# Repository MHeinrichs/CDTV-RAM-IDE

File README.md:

[This project moved to gitlab on the day M$ bought github](https://gitlab.com/MHeinrichs/CDTV-RAM-IDE)

The new repository is at: https://gitlab.com/MHeinrichs/CDTV-RAM-IDE

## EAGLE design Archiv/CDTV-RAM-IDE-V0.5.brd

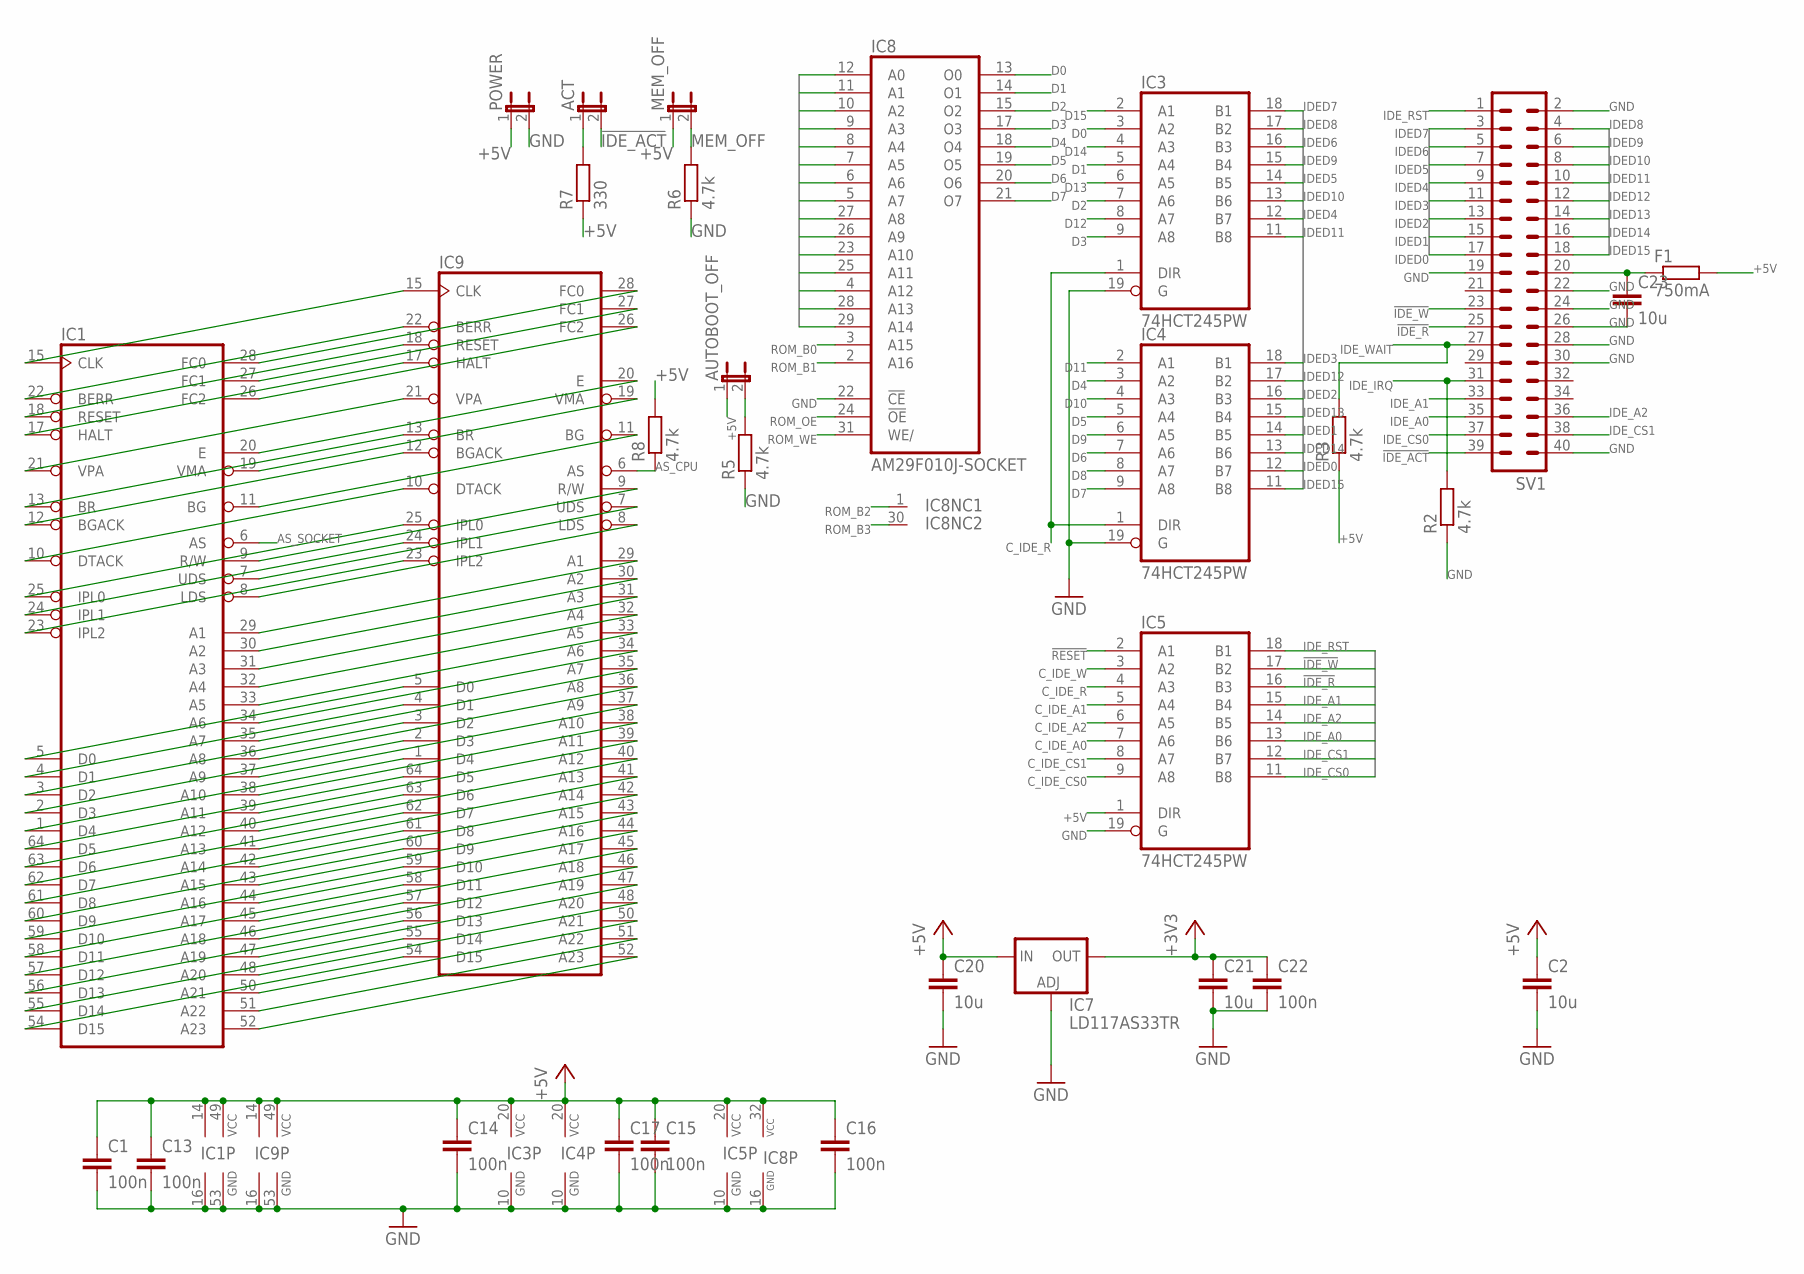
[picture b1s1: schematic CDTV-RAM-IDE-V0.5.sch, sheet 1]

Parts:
ACT: JP1E; JP1
AUTOBOOT_OFF: JP1E; JP1
C1, C13, C14, C15, C16, C17, C22: 100n; C0603K
C2, C20, C21, C23: 10u; C0805K
F1: 750mA; R2512
IC1, IC9: MC68000PROUND-PAD-BIG-HOLE; DIL64-ROUND-BIGHOLE
IC3, IC4, IC5: 74HCT245PW; TSSOP20
IC7: LD117AS33TR; SOT223
IC8: AM29F010J-SOCKET; PLCC-32-SMT-TT
MEM_OFF: JP1E; JP1
POWER: JP1E; JP1
R2, R3, R5, R6, R8: 4.7k; R0603
R7: 330; R0603
SV1: ML40

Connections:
!BERR: IC1.22 (BERR), IC9.22 (BERR); also elsewhere on the board
!BG: IC1.11 (BG), IC9.11 (BG)
!BGACK: IC1.12 (BGACK), IC9.12 (BGACK); also elsewhere on the board
!BR: IC1.13 (BR), IC9.13 (BR)
!DTACK: IC1.10 (DTACK), IC9.10 (DTACK); also elsewhere on the board
!HALT: IC1.17 (HALT), IC9.17 (HALT)
!IDE_ACT: ACT.2, SV1.39
!IDE_R: IC5.16 (B3), SV1.25
!IDE_W: IC5.17 (B2), SV1.23
!LDS: IC1.8 (LDS), IC9.8 (LDS); also elsewhere on the board
!RESET: IC1.18 (RESET), IC5.2 (A1), IC9.18 (RESET); also elsewhere on the board
!UDS: IC1.7 (UDS), IC9.7 (UDS); also elsewhere on the board
+3V3: C21.1, C22.1, IC7.2 (OUT), IC7.4 (OUT); also elsewhere on the board
+5V: AUTOBOOT_OFF.1, C1.1, C2.1, C13.1, C14.1, C15.1, C16.1, C17.1, C20.1, F1.2, IC1.14 (VCC), IC1.49 (VCC), IC3.20 (VCC), IC4.20 (VCC), IC5.1 (DIR), IC5.20 (VCC), IC7.3 (IN), IC8.32 (VCC), IC9.14 (VCC), IC9.49 (VCC), MEM_OFF.1, POWER.1, R3.1, R7.1, R8.2; also elsewhere on the board
A1: IC1.29 (A1), IC8.12 (A0), IC9.29 (A1); also elsewhere on the board
A2: IC1.30 (A2), IC8.11 (A1), IC9.30 (A2); also elsewhere on the board
A3: IC1.31 (A3), IC8.10 (A2), IC9.31 (A3); also elsewhere on the board
A4: IC1.32 (A4), IC8.9 (A3), IC9.32 (A4); also elsewhere on the board
A5: IC1.33 (A5), IC8.8 (A4), IC9.33 (A5); also elsewhere on the board
A6: IC1.34 (A6), IC8.7 (A5), IC9.34 (A6); also elsewhere on the board
A7: IC1.35 (A7), IC8.6 (A6), IC9.35 (A7); also elsewhere on the board
A8: IC1.36 (A8), IC8.5 (A7), IC9.36 (A8); also elsewhere on the board
A9: IC1.37 (A9), IC8.27 (A8), IC9.37 (A9); also elsewhere on the board
A10: IC1.38 (A10), IC8.26 (A9), IC9.38 (A10); also elsewhere on the board
A11: IC1.39 (A11), IC8.23 (A10), IC9.39 (A11); also elsewhere on the board
A12: IC1.40 (A12), IC8.25 (A11), IC9.40 (A12); also elsewhere on the board
A13: IC1.41 (A13), IC8.4 (A12), IC9.41 (A13); also elsewhere on the board
A14: IC1.42 (A14), IC8.28 (A13), IC9.42 (A14); also elsewhere on the board
A15: IC1.43 (A15), IC8.29 (A14), IC9.43 (A15); also elsewhere on the board
A16: IC1.44 (A16), IC9.44 (A16); also elsewhere on the board
A17: IC1.45 (A17), IC9.45 (A17); also elsewhere on the board
A18: IC1.46 (A18), IC9.46 (A18); also elsewhere on the board
A19: IC1.47 (A19), IC9.47 (A19); also elsewhere on the board
A20: IC1.48 (A20), IC9.48 (A20); also elsewhere on the board
A21: IC1.50 (A21), IC9.50 (A21); also elsewhere on the board
A22: IC1.51 (A22), IC9.51 (A22); also elsewhere on the board
A23: IC1.52 (A23), IC9.52 (A23); also elsewhere on the board
AS_CPU: IC9.6 (AS), R8.1; also elsewhere on the board
AS_SOCKET: IC1.6 (AS); also elsewhere on the board
AUTO_BOOT_OFF: AUTOBOOT_OFF.2, R5.2; also elsewhere on the board
CLK: IC1.15 (CLK), IC9.15 (CLK); also elsewhere on the board
C_IDE_A0: IC5.7 (A6); also elsewhere on the board
C_IDE_A1: IC5.5 (A4); also elsewhere on the board
C_IDE_A2: IC5.6 (A5); also elsewhere on the board
C_IDE_CS0: IC5.9 (A8); also elsewhere on the board
C_IDE_CS1: IC5.8 (A7); also elsewhere on the board
C_IDE_R: IC3.1 (DIR), IC4.1 (DIR), IC5.4 (A3); also elsewhere on the board
C_IDE_W: IC5.3 (A2); also elsewhere on the board
D0: IC1.5 (D0), IC3.3 (A2), IC8.13 (O0), IC9.5 (D0); also elsewhere on the board
D1: IC1.4 (D1), IC3.5 (A4), IC8.14 (O1), IC9.4 (D1); also elsewhere on the board
D2: IC1.3 (D2), IC3.7 (A6), IC8.15 (O2), IC9.3 (D2); also elsewhere on the board
D3: IC1.2 (D3), IC3.9 (A8), IC8.17 (O3), IC9.2 (D3); also elsewhere on the board
D4: IC1.1 (D4), IC4.3 (A2), IC8.18 (O4), IC9.1 (D4); also elsewhere on the board
D5: IC1.64 (D5), IC4.5 (A4), IC8.19 (O5), IC9.64 (D5); also elsewhere on the board
D6: IC1.63 (D6), IC4.7 (A6), IC8.20 (O6), IC9.63 (D6); also elsewhere on the board
D7: IC1.62 (D7), IC4.9 (A8), IC8.21 (O7), IC9.62 (D7); also elsewhere on the board
D8: IC1.61 (D8), IC4.8 (A7), IC9.61 (D8); also elsewhere on the board
D9: IC1.60 (D9), IC4.6 (A5), IC9.60 (D9); also elsewhere on the board
D10: IC1.59 (D10), IC4.4 (A3), IC9.59 (D10); also elsewhere on the board
D11: IC1.58 (D11), IC4.2 (A1), IC9.58 (D11); also elsewhere on the board
D12: IC1.57 (D12), IC3.8 (A7), IC9.57 (D12); also elsewhere on the board
D13: IC1.56 (D13), IC3.6 (A5), IC9.56 (D13); also elsewhere on the board
D14: IC1.55 (D14), IC3.4 (A3), IC9.55 (D14); also elsewhere on the board
D15: IC1.54 (D15), IC3.2 (A1), IC9.54 (D15); also elsewhere on the board
E: IC1.20 (E), IC9.20 (E)
FC0: IC1.28 (FC0), IC9.28 (FC0)
FC1: IC1.27 (FC1), IC9.27 (FC1)
FC2: IC1.26 (FC2), IC9.26 (FC2)
GND: C1.2, C2.2, C13.2, C14.2, C15.2, C16.2, C17.2, C20.2, C21.2, C22.2, C23.2, IC1.16 (GND), IC1.53 (GND), IC3.10 (GND), IC3.19 (G), IC4.10 (GND), IC4.19 (G), IC5.10 (GND), IC5.19 (G), IC7.1 (ADJ), IC8.16 (GND), IC8.22 (!CE), IC9.16 (GND), IC9.53 (GND), POWER.2, R2.1, R5.1, R6.1, SV1.2, SV1.19, SV1.22, SV1.24, SV1.26, SV1.28, SV1.30, SV1.40; also elsewhere on the board
IDED0: IC4.12 (B7), SV1.17
IDED1: IC4.14 (B5), SV1.15
IDED2: IC4.16 (B3), SV1.13
IDED3: IC4.18 (B1), SV1.11
IDED4: IC3.12 (B7), SV1.9
IDED5: IC3.14 (B5), SV1.7
IDED6: IC3.16 (B3), SV1.5
IDED7: IC3.18 (B1), SV1.3
IDED8: IC3.17 (B2), SV1.4
IDED9: IC3.15 (B4), SV1.6
IDED10: IC3.13 (B6), SV1.8
IDED11: IC3.11 (B8), SV1.10
IDED12: IC4.17 (B2), SV1.12
IDED13: IC4.15 (B4), SV1.14
IDED14: IC4.13 (B6), SV1.16
IDED15: IC4.11 (B8), SV1.18
IDE_A0: IC5.13 (B6), SV1.35
IDE_A1: IC5.15 (B4), SV1.33
IDE_A2: IC5.14 (B5), SV1.36
IDE_CS0: IC5.11 (B8), SV1.37
IDE_CS1: IC5.12 (B7), SV1.38
IDE_IRQ: R2.2, SV1.31; also elsewhere on the board
IDE_RST: IC5.18 (B1), SV1.1
IDE_WAIT: R3.2, SV1.27; also elsewhere on the board
IPL0: IC1.25 (IPL0), IC9.25 (IPL0)
IPL1: IC1.24 (IPL1), IC9.24 (IPL1)
IPL2: IC1.23 (IPL2), IC9.23 (IPL2)
KEY_PIN_POWER: C23.1, F1.1, SV1.20
MEM_OFF: MEM_OFF.2, R6.2; also elsewhere on the board
unnamed: ACT.1, R7.2
R/W: IC1.9 (R/W), IC9.9 (R/W); also elsewhere on the board
ROM_B0: IC8.3 (A15); also elsewhere on the board
ROM_B1: IC8.2 (A16); also elsewhere on the board
ROM_B2: IC8.1 (NC); also elsewhere on the board
ROM_B3: IC8.30 (NC); also elsewhere on the board
ROM_OE: IC8.24 (!OE); also elsewhere on the board
ROM_WE: IC8.31 (WE/); also elsewhere on the board
VMA: IC1.19 (VMA), IC9.19 (VMA)
VPA: IC1.21 (VPA), IC9.21 (VPA)

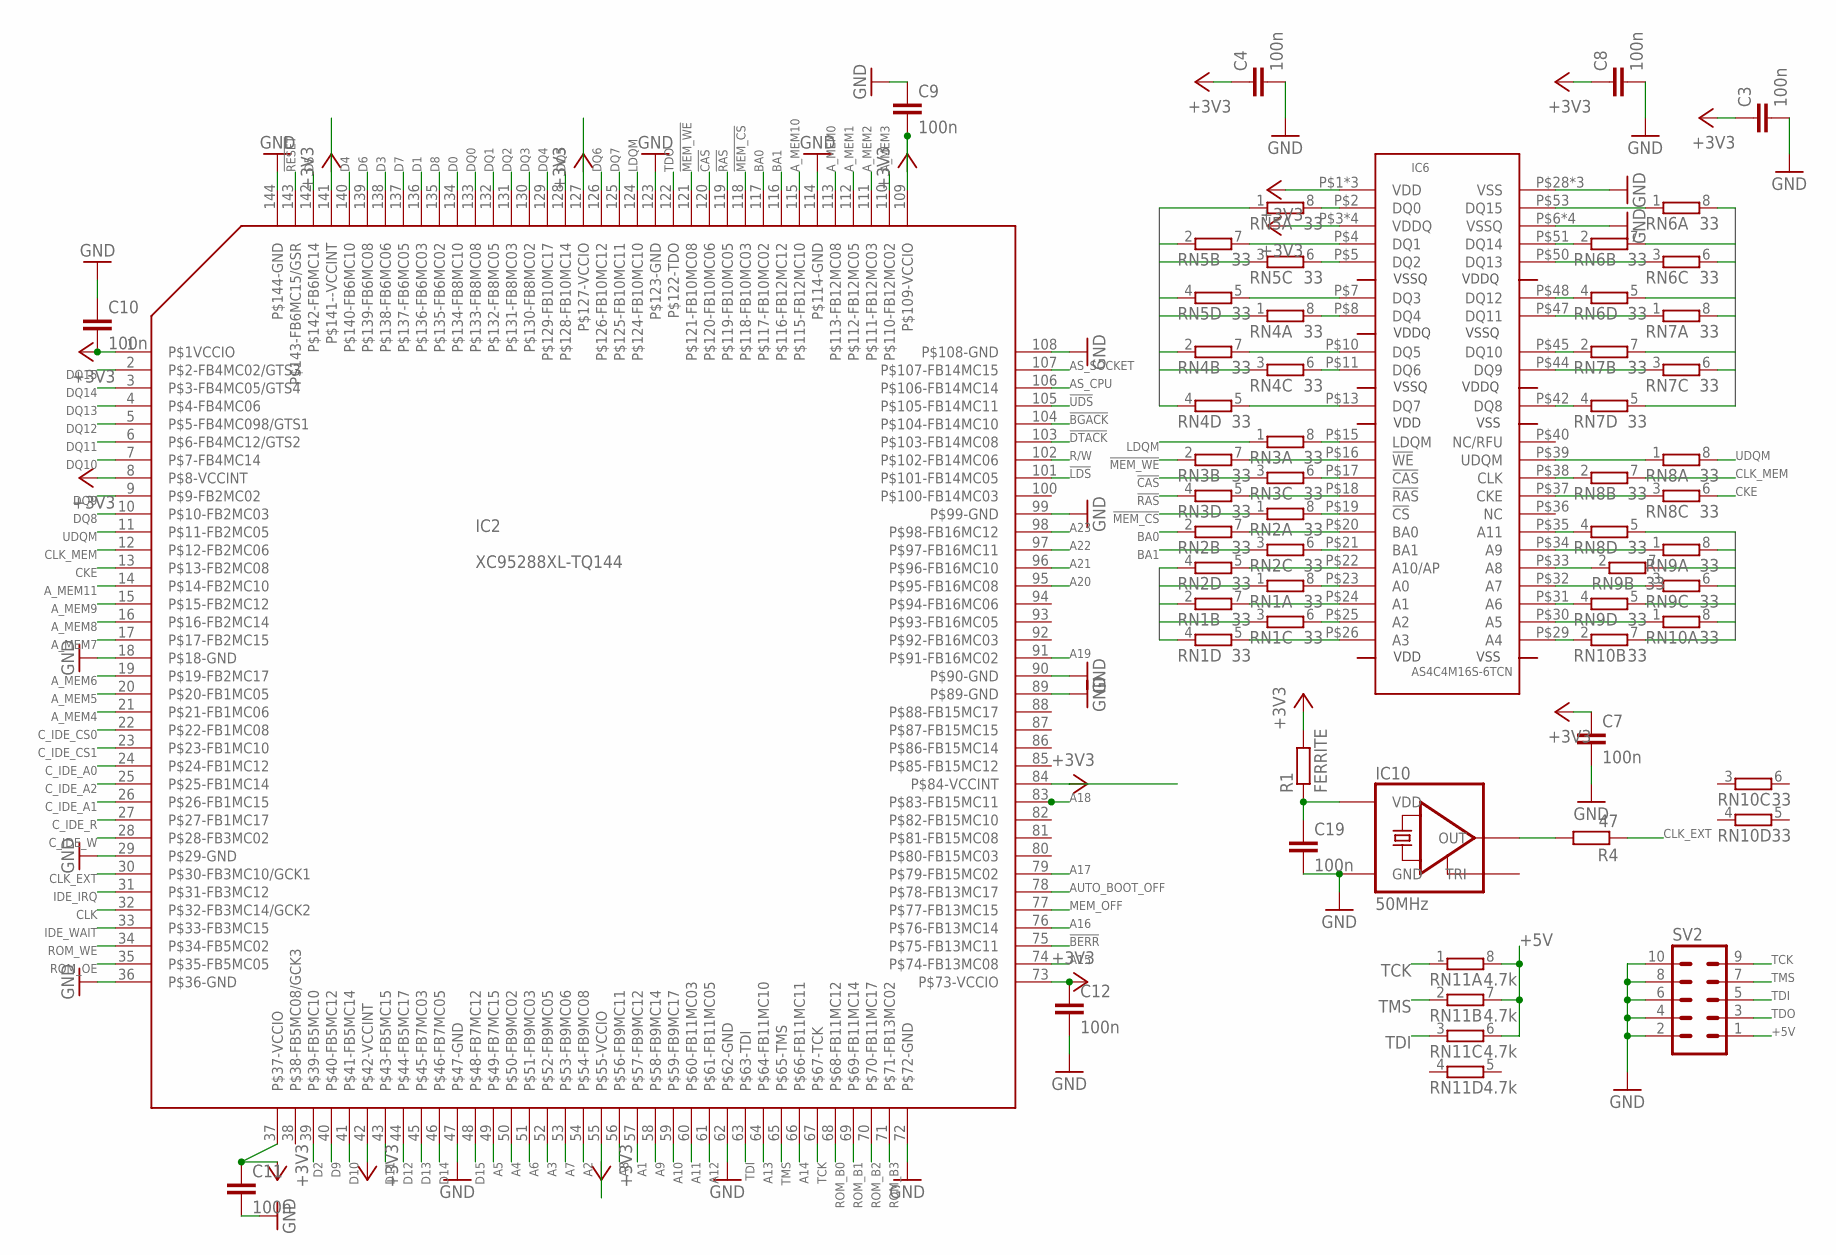
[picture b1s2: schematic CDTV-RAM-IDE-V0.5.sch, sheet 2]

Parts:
C3, C4, C7, C8, C9, C10, C11, C12, C19: 100n; C0603K
IC2: XC95288XL-TQ144; TQFP144
IC6: AS4C4M16S-6TCN; TSOP-2_54
IC10: 50MHz; 7X5
R1: FERRITE; R0603
R4: 47; R0603
RN1, RN2, RN3, RN4, RN5, RN6, RN7, RN8, RN9, RN10: 33; CAY16
RN11: 4.7k; CAY16
SV2: ML10L

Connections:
!BERR: IC2.75 (P$75-FB13MC11); also elsewhere on the board
!BGACK: IC2.104 (P$104-FB14MC10); also elsewhere on the board
!CAS: IC2.120 (P$120-FB10MC06), RN3.3 (1)
!DTACK: IC2.103 (P$103-FB14MC08); also elsewhere on the board
!LDS: IC2.101 (P$101-FB14MC05); also elsewhere on the board
!MEM_CS: IC2.118 (P$118-FB10MC03), RN2.1
!MEM_WE: IC2.121 (P$121-FB10MC08), RN3.2 (1)
!RAS: IC2.119 (P$119-FB10MC05), RN3.4 (1)
!RESET: IC2.143 (P$143-FB6MC15/GSR); also elsewhere on the board
!UDS: IC2.105 (P$105-FB14MC11); also elsewhere on the board
+3V3: C3.1, C4.1, C7.1, C8.1, C9.2, C10.2, C11.1, C12.1, IC2.1 (P$1VCCIO), IC2.8 (P$8-VCCINT), IC2.37 (P$37-VCCIO), IC2.42 (P$42-VCCINT), IC2.55 (P$55-VCCIO), IC2.73 (P$73-VCCIO), IC2.84 (P$84-VCCINT), IC2.109 (P$109-VCCIO), IC2.127 (P$127-VCCIO), IC2.141 (P$141--VCCINT), IC6.P$1 (VDD), IC6.P$3 (VDDQ), IC6.P$9 (VDDQ), IC6.P$14 (VDD), IC6.P$27 (VDD), IC6.P$43 (VDDQ), IC6.P$49 (VDDQ), R1.2; also elsewhere on the board
+5V: RN11.6 (2), RN11.7 (2), RN11.8 (2), SV2.1; also elsewhere on the board
A1: IC2.57 (P$57-FB9MC12); also elsewhere on the board
A2: IC2.54 (P$54-FB9MC08); also elsewhere on the board
A3: IC2.52 (P$52-FB9MC05); also elsewhere on the board
A4: IC2.50 (P$50-FB9MC02); also elsewhere on the board
A5: IC2.49 (P$49-FB7MC15); also elsewhere on the board
A6: IC2.51 (P$51-FB9MC03); also elsewhere on the board
A7: IC2.53 (P$53-FB9MC06); also elsewhere on the board
A8: IC2.56 (P$56-FB9MC11); also elsewhere on the board
A9: IC2.58 (P$58-FB9MC14); also elsewhere on the board
A10: IC2.59 (P$59-FB9MC17); also elsewhere on the board
A11: IC2.60 (P$60-FB11MC03); also elsewhere on the board
A12: IC2.61 (P$61-FB11MC05); also elsewhere on the board
A13: IC2.64 (P$64-FB11MC10); also elsewhere on the board
A14: IC2.66 (P$66-FB11MC11); also elsewhere on the board
A15: IC2.74 (P$74-FB13MC08); also elsewhere on the board
A16: IC2.76 (P$76-FB13MC14); also elsewhere on the board
A17: IC2.79 (P$79-FB15MC02); also elsewhere on the board
A18: IC2.83 (P$83-FB15MC11); also elsewhere on the board
A19: IC2.91 (P$91-FB16MC02); also elsewhere on the board
A20: IC2.95 (P$95-FB16MC08); also elsewhere on the board
A21: IC2.96 (P$96-FB16MC10); also elsewhere on the board
A22: IC2.97 (P$97-FB16MC11); also elsewhere on the board
A23: IC2.98 (P$98-FB16MC12); also elsewhere on the board
AS_CPU: IC2.106 (P$106-FB14MC14); also elsewhere on the board
AS_SOCKET: IC2.107 (P$107-FB14MC15); also elsewhere on the board
AUTO_BOOT_OFF: IC2.78 (P$78-FB13MC17); also elsewhere on the board
A_MEM0: IC2.113 (P$113-FB12MC08), RN1.1
A_MEM1: IC2.112 (P$112-FB12MC05), RN1.2 (1)
A_MEM2: IC2.111 (P$111-FB12MC03), RN1.3 (1)
A_MEM3: IC2.110 (P$110-FB12MC02), RN1.4 (1)
A_MEM4: IC2.21 (P$21-FB1MC06), RN10.7 (2)
A_MEM5: IC2.20 (P$20-FB1MC05), RN10.8 (2)
A_MEM6: IC2.19 (P$19-FB2MC17), RN9.5 (2)
A_MEM7: IC2.17 (P$17-FB2MC15), RN9.6 (2)
A_MEM8: IC2.16 (P$16-FB2MC14), RN9.7 (2)
A_MEM9: IC2.15 (P$15-FB2MC12), RN9.8 (2)
A_MEM10: IC2.115 (P$115-FB12MC10), RN2.4 (1)
A_MEM11: IC2.14 (P$14-FB2MC10), RN8.5 (2)
BA0: IC2.117 (P$117-FB10MC02), RN2.2 (1)
BA1: IC2.116 (P$116-FB12MC12), RN2.3 (1)
CKE: IC2.13 (P$13-FB2MC08), RN8.6 (2)
CLK: IC2.32 (P$32-FB3MC14/GCK2); also elsewhere on the board
CLK_EXT: IC2.30 (P$30-FB3MC10/GCK1), R4.1
CLK_MEM: IC2.12 (P$12-FB2MC06), RN8.7 (2)
C_IDE_A0: IC2.24 (P$24-FB1MC12); also elsewhere on the board
C_IDE_A1: IC2.26 (P$26-FB1MC15); also elsewhere on the board
C_IDE_A2: IC2.25 (P$25-FB1MC14); also elsewhere on the board
C_IDE_CS0: IC2.22 (P$22-FB1MC08); also elsewhere on the board
C_IDE_CS1: IC2.23 (P$23-FB1MC10); also elsewhere on the board
C_IDE_R: IC2.27 (P$27-FB1MC17); also elsewhere on the board
C_IDE_W: IC2.28 (P$28-FB3MC02); also elsewhere on the board
D0: IC2.134 (P$134-FB8MC10); also elsewhere on the board
D1: IC2.136 (P$136-FB6MC03); also elsewhere on the board
D2: IC2.39 (P$39-FB5MC10); also elsewhere on the board
D3: IC2.138 (P$138-FB6MC06); also elsewhere on the board
D4: IC2.140 (P$140-FB6MC10); also elsewhere on the board
D5: IC2.142 (P$142-FB6MC14); also elsewhere on the board
D6: IC2.139 (P$139-FB6MC08); also elsewhere on the board
D7: IC2.137 (P$137-FB6MC05); also elsewhere on the board
D8: IC2.135 (P$135-FB6MC02); also elsewhere on the board
D9: IC2.40 (P$40-FB5MC12); also elsewhere on the board
D10: IC2.41 (P$41-FB5MC14); also elsewhere on the board
D11: IC2.43 (P$43-FB5MC15); also elsewhere on the board
D12: IC2.44 (P$44-FB5MC17); also elsewhere on the board
D13: IC2.45 (P$45-FB7MC03); also elsewhere on the board
D14: IC2.46 (P$46-FB7MC05); also elsewhere on the board
D15: IC2.48 (P$48-FB7MC12); also elsewhere on the board
DQ0: IC2.133 (P$133-FB8MC08), RN5.1
DQ1: IC2.132 (P$132-FB8MC05), RN5.2 (1)
DQ2: IC2.131 (P$131-FB8MC03), RN5.3 (1)
DQ3: IC2.130 (P$130-FB8MC02), RN5.4 (1)
DQ4: IC2.129 (P$129-FB10MC17), RN4.1
DQ5: IC2.128 (P$128-FB10MC14), RN4.2 (1)
DQ6: IC2.126 (P$126-FB10MC12), RN4.3 (1)
DQ7: IC2.125 (P$125-FB10MC11), RN4.4 (1)
DQ8: IC2.10 (P$10-FB2MC03), RN7.5 (2)
DQ9: IC2.9 (P$9-FB2MC02), RN7.6 (2)
DQ10: IC2.7 (P$7-FB4MC14), RN7.7 (2)
DQ11: IC2.6 (P$6-FB4MC12/GTS2), RN7.8 (2)
DQ12: IC2.5 (P$5-FB4MC098/GTS1), RN6.5 (2)
DQ13: IC2.4 (P$4-FB4MC06), RN6.6 (2)
DQ14: IC2.3 (P$3-FB4MC05/GTS4), RN6.7 (2)
DQ15: IC2.2 (P$2-FB4MC02/GTS3), RN6.8 (2)
GND: C3.2, C4.2, C7.2, C8.2, C9.1, C10.1, C11.2, C12.2, C19.2, IC2.18 (P$18-GND), IC2.29 (P$29-GND), IC2.36 (P$36-GND), IC2.47 (P$47-GND), IC2.62 (P$62-GND), IC2.72 (P$72-GND), IC2.89 (P$89-GND), IC2.90 (P$90-GND), IC2.99 (P$99-GND), IC2.108 (P$108-GND), IC2.114 (P$114-GND), IC2.123 (P$123-GND), IC2.144 (P$144-GND), IC6.P$6 (VSSQ), IC6.P$12 (VSSQ), IC6.P$28 (VSS), IC6.P$41 (VSS), IC6.P$46 (VSSQ), IC6.P$52 (VSSQ), IC6.P$54 (VSS), IC10.P$2 (GND), SV2.2, SV2.4, SV2.6, SV2.8, SV2.10; also elsewhere on the board
IDE_IRQ: IC2.31 (P$31-FB3MC12); also elsewhere on the board
IDE_WAIT: IC2.33 (P$33-FB3MC15); also elsewhere on the board
LDQM: IC2.124 (P$124-FB10MC10), RN3.1
MEM_OFF: IC2.77 (P$77-FB13MC15); also elsewhere on the board
unnamed: IC6.P$26 (A3), RN1.5 (2)
unnamed: IC6.P$25 (A2), RN1.6 (2)
unnamed: IC6.P$24 (A1), RN1.7 (2)
unnamed: IC6.P$23 (A0), RN1.8 (2)
unnamed: IC6.P$22 (A10/AP), RN2.5 (2)
unnamed: IC6.P$21 (BA1), RN2.6 (2)
unnamed: IC6.P$20 (BA0), RN2.7 (2)
unnamed: IC6.P$19 (!CS), RN2.8 (2)
unnamed: IC6.P$18 (!RAS), RN3.5 (2)
unnamed: IC6.P$17 (!CAS), RN3.6 (2)
unnamed: IC6.P$16 (!WE), RN3.7 (2)
unnamed: IC6.P$15 (LDQM), RN3.8 (2)
unnamed: IC6.P$13 (DQ7), RN4.5 (2)
unnamed: IC6.P$11 (DQ6), RN4.6 (2)
unnamed: IC6.P$10 (DQ5), RN4.7 (2)
unnamed: IC6.P$8 (DQ4), RN4.8 (2)
unnamed: IC6.P$7 (DQ3), RN5.5 (2)
unnamed: IC6.P$5 (DQ2), RN5.6 (2)
unnamed: IC6.P$4 (DQ1), RN5.7 (2)
unnamed: IC6.P$2 (DQ0), RN5.8 (2)
unnamed: IC6.P$53 (DQ15), RN6.1
unnamed: IC6.P$51 (DQ14), RN6.2 (1)
unnamed: IC6.P$50 (DQ13), RN6.3 (1)
unnamed: IC6.P$48 (DQ12), RN6.4 (1)
unnamed: IC6.P$47 (DQ11), RN7.1
unnamed: IC6.P$45 (DQ10), RN7.2 (1)
unnamed: IC6.P$44 (DQ9), RN7.3 (1)
unnamed: IC6.P$42 (DQ8), RN7.4 (1)
unnamed: IC6.P$39 (UDQM), RN8.1
unnamed: IC6.P$38 (CLK), RN8.2 (1)
unnamed: IC6.P$37 (CKE), RN8.3 (1)
unnamed: IC6.P$35 (A11), RN8.4 (1)
unnamed: IC6.P$34 (A9), RN9.1
unnamed: IC6.P$33 (A8), RN9.2 (1)
unnamed: IC6.P$32 (A7), RN9.3 (1)
unnamed: IC6.P$31 (A6), RN9.4 (1)
unnamed: IC6.P$30 (A5), RN10.1
unnamed: IC6.P$29 (A4), RN10.2 (1)
unnamed: IC10.P$3 (OUT), R4.2
R/W: IC2.102 (P$102-FB14MC06); also elsewhere on the board
ROM_B0: IC2.68 (P$68-FB11MC12); also elsewhere on the board
ROM_B1: IC2.69 (P$69-FB11MC14); also elsewhere on the board
ROM_B2: IC2.70 (P$70-FB11MC17); also elsewhere on the board
ROM_B3: IC2.71 (P$71-FB13MC02); also elsewhere on the board
ROM_OE: IC2.35 (P$35-FB5MC05); also elsewhere on the board
ROM_WE: IC2.34 (P$34-FB5MC02); also elsewhere on the board
TCK: IC2.67 (P$67-TCK), RN11.1, SV2.9
TDI: IC2.63 (P$63-TDI), RN11.3 (1), SV2.5
TDO: IC2.122 (P$122-TDO), SV2.3
TMS: IC2.65 (P$65-TMS), RN11.2 (1), SV2.7
UDQM: IC2.11 (P$11-FB2MC05), RN8.8 (2)
VCC-X: C19.1, IC10.P$4 (VDD), R1.1

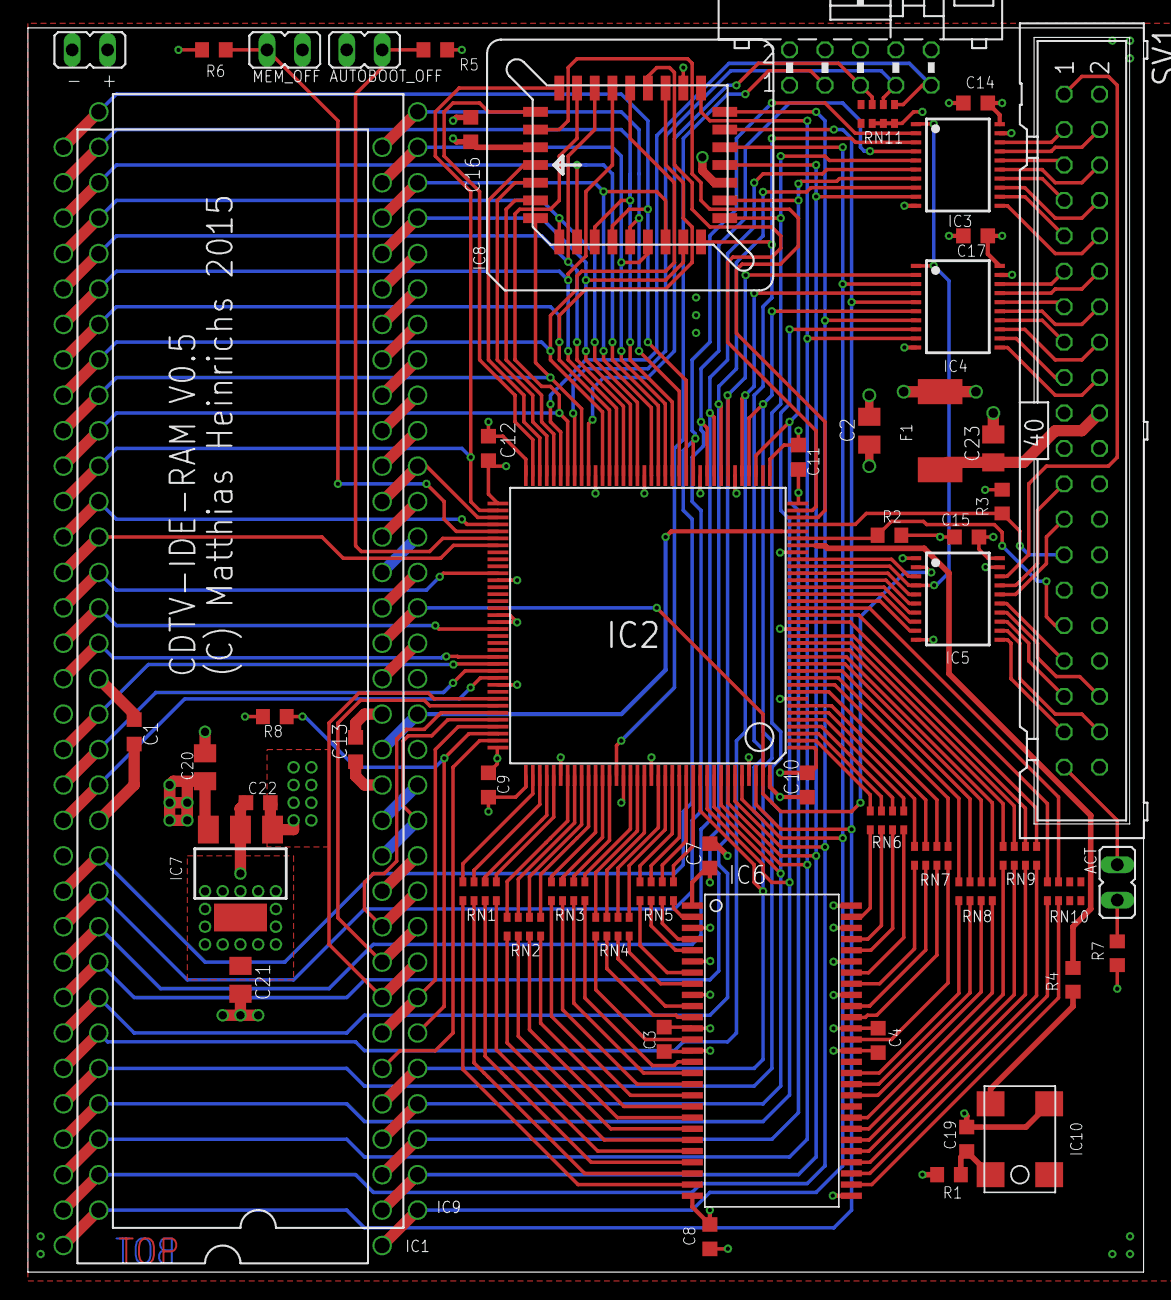
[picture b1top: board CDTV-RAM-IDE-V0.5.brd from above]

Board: 4 copper layers, 80.0 x 89.2 mm, 56 parts (0 on the bottom side), 191 nets.

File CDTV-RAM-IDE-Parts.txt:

Stückliste exportiert aus C:/Users/Matze/Amiga/Hardwarehacks/CDTV-RAM-IDE/CDTV-RAM-IDE-V0.6.sch am 19.08.2016 20:59:36

Qty Value            Device                     Package             Parts                                                                    Description                                                                                    MF MPN OC_FARNELL OC_NEWARK
4                    JP1E                       JP1                 ACT, AUTOBOOT_OFF, MEM_OFF, POWER                                        JUMPER                                                                                                                    
1                    JP1E_ROUND                 JP1-ROUND           OKTA                                                                     JUMPER                                                                                                                    
2                    MC68000PROUND-PAD-BIG-HOLE DIL64-ROUND-BIGHOLE IC1, IC9                                                                 68xxx PROCESSOR                                                                                                           
1                    ML10L                      ML10L               SV2                                                                      HARTING                                                                                               unknown    unknown  
1                    ML40                       ML40                SV1                                                                      HARTING                                                                                               unknown    unknown  
1                    SJ                         SJ                  SJ1                                                                      SMD solder JUMPER                                                                                                         
16  100n             C-EUC0603K                 C0603K              C1, C3, C4, C7, C8, C9, C10, C11, C12, C13, C14, C15, C16, C17, C19, C22 CAPACITOR, European symbol                                                                                                
4   10u              C-EUC0805K                 C0805K              C2, C20, C21, C23                                                        CAPACITOR, European symbol                                                                                                
10  33               4R-NCAY16                  CAY16               RN1, RN2, RN3, RN4, RN5, RN6, RN7, RN8, RN9, RN10                        Array Chip Resistor                                                                                   unknown    unknown  
1   330              R-EU_R0603                 R0603               R7                                                                       RESISTOR, European symbol                                                                                                 
1   4.7k             4R-NCAY16                  CAY16               RN11                                                                     Array Chip Resistor                                                                                   unknown    unknown  
6   4.7k             R-EU_R0603                 R0603               R2, R3, R5, R6, R8, R9                                                   RESISTOR, European symbol                                                                                                 
1   47               R-EU_R0603                 R0603               R4                                                                       RESISTOR, European symbol                                                                                                 
1   50MHz            CSX-750FCFC(5V)            7X5                 IC10                                                                     CITIZEN Crystal Clock Oscilator from http://cfm.citizen.co.jp/english/product/pdf/CSX-750F.pdf                            
3   74HCT245PW       74HCT245PW                 TSSOP20             IC3, IC4, IC5                                                            Octal BUS TRANSCEIVER, 3-state                                                                                            
1   750mA            R-EU_R2512                 R2512               F1                                                                       RESISTOR, European symbol                                                                                                 
1   AM29F010J-SOCKET AM29F010J-SOCKET           PLCC-32-SMT-TT      IC8                                                                      1-Megabit FLASH MEMORY                                                                                                    
1   AS4C4M16S-6TCN   AS4C4M16S-6TCN             TSOP-2_54           IC6                                                                                                                                                                                                
1   FERRITE          R-EU_R0603                 R0603               R1                                                                       RESISTOR, European symbol                                                                                                 
1   LD117AS33TR      LD117AS33TR                SOT223              IC7                                                                      Low drop fixed and adjustable positive voltage regulators 1 A                                                             
1   XC95288XL-TQ144  XC95288XL-TQ144            TQFP144             IC2

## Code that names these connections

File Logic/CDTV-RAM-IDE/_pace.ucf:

#amiga busses
NET "D[0]" LOC = "P134";
NET "D[1]" LOC = "P136";
NET "D[2]" LOC = "P39";
NET "D[3]" LOC = "P138";
NET "D[4]" LOC = "P140";
NET "D[5]" LOC = "P142";
NET "D[6]" LOC = "P139";
NET "D[7]" LOC = "P137";
NET "D[8]" LOC = "P135";
NET "D[9]" LOC = "P40";
NET "D[10]" LOC = "P41";
NET "D[11]" LOC = "P43";
NET "D[12]" LOC = "P44";
NET "D[13]" LOC = "P45";
NET "D[14]" LOC = "P46";
NET "D[15]" LOC = "P48";
NET "A[1]"  LOC = "P57";
NET "A[2]"  LOC = "P54";
NET "A[3]"  LOC = "P52";
NET "A[4]"  LOC = "P50";
NET "A[5]"  LOC = "P49";
NET "A[6]"  LOC = "P51";
NET "A[7]"  LOC = "P53";
NET "A[8]"  LOC = "P56";
NET "A[9]"  LOC = "P58";
NET "A[10]"  LOC = "P59";
NET "A[11]"  LOC = "P60";
NET "A[12]"  LOC = "P61";
NET "A[13]"  LOC = "P64";
NET "A[14]"  LOC = "P66";
NET "A[15]"  LOC = "P74";
NET "A[16]"  LOC = "P76";
NET "A[17]"  LOC = "P79";
NET "A[18]"  LOC = "P83";
NET "A[19]"  LOC = "P91";
NET "A[20]"  LOC = "P95";
NET "A[21]"  LOC = "P96";
NET "A[22]"  LOC = "P97";
NET "A[23]"  LOC = "P98";
#amiga signals
NET "AS"  LOC = "P106";
NET "AS_AMIGA"  LOC = "P107";
NET "UDS"  LOC = "P105";
NET "LDS"  LOC = "P101";
NET "RW"  LOC = "P102";
NET "DTACK"  LOC = "P103";
NET "BERR"  LOC = "P75";
NET "BGACK"  LOC = "P104";
NET "AMIGA_CLK"  LOC = "P32";
NET reset LOC = "P143";
#RAM signals
NET "DRAM[0]" LOC = "P133";
NET "DRAM[1]" LOC = "P132";
NET "DRAM[2]" LOC = "P131";
NET "DRAM[3]" LOC = "P130";
NET "DRAM[4]" LOC = "P129";
NET "DRAM[5]" LOC = "P128";
NET "DRAM[6]" LOC = "P126";
NET "DRAM[7]" LOC = "P125";
NET "DRAM[8]" LOC = "P10";
NET "DRAM[9]" LOC = "P9";
NET "DRAM[10]" LOC = "P7";
NET "DRAM[11]" LOC = "P6";
NET "DRAM[12]" LOC = "P5";
NET "DRAM[13]" LOC = "P4";
NET "DRAM[14]" LOC = "P3";
NET "DRAM[15]" LOC = "P2";
NET "ARAM[0]"  LOC = "P113";
NET "ARAM[1]"  LOC = "P112";
NET "ARAM[2]"  LOC = "P111";
NET "ARAM[3]"  LOC = "P110";
NET "ARAM[4]"  LOC = "P21";
NET "ARAM[5]"  LOC = "P20";
NET "ARAM[6]"  LOC = "P19";
NET "ARAM[7]"  LOC = "P17";
NET "ARAM[8]"  LOC = "P16";
NET "ARAM[9]"  LOC = "P15";
NET "ARAM[10]"  LOC = "P115";
NET "ARAM[11]"  LOC = "P14";
NET "BA[0]"  LOC = "P117";
NET "BA[1]"  LOC = "P116";
NET "LDQM"  LOC = "P124";
NET "UDQM"  LOC = "P11";
NET "CKE"  LOC = "P13";
NET "CLK_MEM"  LOC = "P12";
NET "MEM_WE"  LOC = "P121";
NET "CAS"  LOC = "P120";
NET "RAS"  LOC = "P119";
NET "MEM_CS"  LOC = "P118";
#IDE signals
NET "IDE_W"  LOC = "P28";
NET "IDE_R"  LOC = "P27";
NET "IDE_CS[0]"  LOC = "P22";
NET "IDE_CS[1]"  LOC = "P23";
NET "IDE_A[0]"  LOC = "P24";
NET "IDE_A[1]"  LOC = "P26";
NET "IDE_A[2]"  LOC = "P25";
NET "IDE_WAIT"  LOC = "P33";
NET "IDE_IRQ"  LOC = "P31";
#rom signals
NET "ROM_BANK[0]"  LOC = "P68";
NET "ROM_BANK[1]"  LOC = "P69";
NET "ROM_BANK[2]"  LOC = "P70";
NET "ROM_BANK[3]"  LOC = "P71";
NET "ROM_WE"  LOC = "P34";
NET "ROM_OE"  LOC = "P35";
#controll signals
NET "MEM_OFF"  LOC = "P77";
NET "IDE_OFF"  LOC = "P78";
NET "CLK50M"  LOC = "P30";

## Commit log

2016-06-26 :space_invader: Added .gitattributes & .gitignore files
2016-06-28 Initial Push
2016-06-28 Other files
2016-06-28 ignore big files
2016-07-05 Strange: It works but only with mem switched off at first boot
2016-07-08 Still same strange error
2016-07-23 even 8192 Refreshes do not change the situation on init :(
2016-07-23 "Working" as ususal
2016-07-24 Reworked OP-Code sectiona d it works now!
2016-07-24 jed remade
2016-08-14 DMA with A590 working
2016-08-14 Working but Autoboot-Problems unter CDTV?!?
2016-08-19 Optimized the PCB and added a Jumper for AT-Bus/Oktapussy
2019-08-28 Moved to gitlab
